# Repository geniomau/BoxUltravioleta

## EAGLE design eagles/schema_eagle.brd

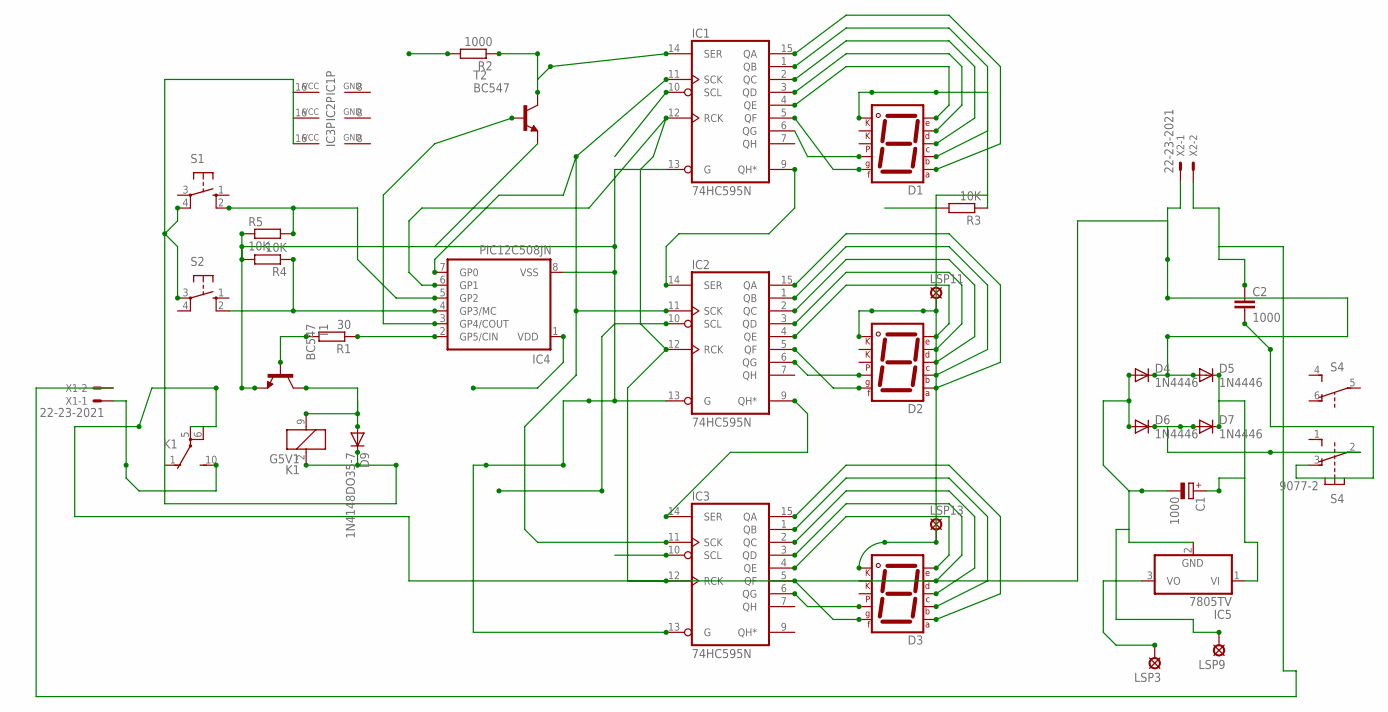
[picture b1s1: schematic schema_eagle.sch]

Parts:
C1: 1000; E5-10,5
C2: 1000; C22.5B7
D1, D2, D3: 7SEG-CK; 7SEG-13
D4, D5, D6, D7: 1N4446; DO35-10
D9: 1N4148DO35-7; DO35-7
IC1, IC2, IC3: 74HC595N; DIL16
IC4: PIC12C508JN; DIL8
IC5: 7805TV; TO220V
K1: G5V1
LSP3: VDD; LSP10
LSP9: GND; LSP10
LSP11, LSP13: 5V; LSP10
R1: 30; 0207/7
R2: 1000; 0207/7
R3, R4, R5: 10K; 0207/7
S1, S2: 10-XX; B3F-10XX
S4: 9077-2
T1, T2: BC547; TO92
X1, X2: 22-23-2021

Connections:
GND: C1.-, D4.A, D6.A, IC1.8 (GND), IC1.13 (G), IC2.8 (GND), IC2.13 (G), IC3.8 (GND), IC3.13 (G), IC4.8 (VSS), IC5.2 (GND), LSP9.MP, R3.2, R4.2, R5.1, T1.1 (E), T2.1 (E)
unnamed: D1.7 (A), IC1.15 (QA)
unnamed: D1.6 (B), IC1.1 (QB)
unnamed: D1.4 (C), IC1.2 (QC)
unnamed: D1.2 (D), IC1.3 (QD)
unnamed: D1.1 (E), IC1.4 (QE)
unnamed: D1.9 (F), IC1.5 (QF)
unnamed: D1.10 (G), IC1.6 (QG)
unnamed: D2.7 (A), IC2.15 (QA)
unnamed: D2.6 (B), IC2.1 (QB)
unnamed: D2.4 (C), IC2.2 (QC)
unnamed: D2.2 (D), IC2.3 (QD)
unnamed: D2.1 (E), IC2.4 (QE)
unnamed: D2.9 (F), IC2.5 (QF)
unnamed: D2.10 (G), IC2.6 (QG)
unnamed: D3.7 (A), IC3.15 (QA)
unnamed: D3.6 (B), IC3.1 (QB)
unnamed: D3.4 (C), IC3.2 (QC)
unnamed: D3.2 (D), IC3.3 (QD)
unnamed: D3.1 (E), IC3.4 (QE)
unnamed: D3.9 (F), IC3.5 (QF)
unnamed: D3.10 (G), IC3.6 (QG)
unnamed: C2.2, S4.3 (O)
unnamed: IC4.4 (GP3/MC), R4.1, S2.2 (S1)
unnamed: IC4.5 (GP2), R5.2, S1.2 (S1)
unnamed: IC1.12 (RCK), IC2.12 (RCK), IC3.12 (RCK), IC4.6 (GP1)
unnamed: IC1.11 (SCK), IC2.11 (SCK), IC3.11 (SCK), IC4.7 (GP0)
unnamed: IC1.14 (SER), R2.1, T2.3 (C)
unnamed: K1.10 (S), X1.1
unnamed: R1.2, T1.2 (B)
unnamed: IC1.9 (QH*), IC2.14 (SER)
unnamed: IC2.9 (QH*), IC3.14 (SER)
unnamed: IC4.3 (GP4/COUT), T2.2 (B)
unnamed: D9.A, K1.9 (2), T1.3 (C)
unnamed: IC4.2 (GP5/CIN), R1.1
unnamed: D4.C, D5.A, K1.5, K1.6, X2.1
unnamed: D1.8 (CK2), D2.8 (CK2), D3.8 (CK2), LSP11.MP, LSP13.MP, R3.1
unnamed: C1.+, D5.C, D7.C, IC5.1 (VI)
unnamed: C2.1, X1.2, X2.2
unnamed: D6.C, D7.A, S4.2
VDD: D9.C, IC1.10 (SCL), IC1.16 (VCC), IC2.10 (SCL), IC2.16 (VCC), IC3.10 (SCL), IC3.16 (VCC), IC4.1 (VDD), IC5.3 (VO), K1.2 (1), LSP3.MP, R2.2, S1.4 (P1), S2.3

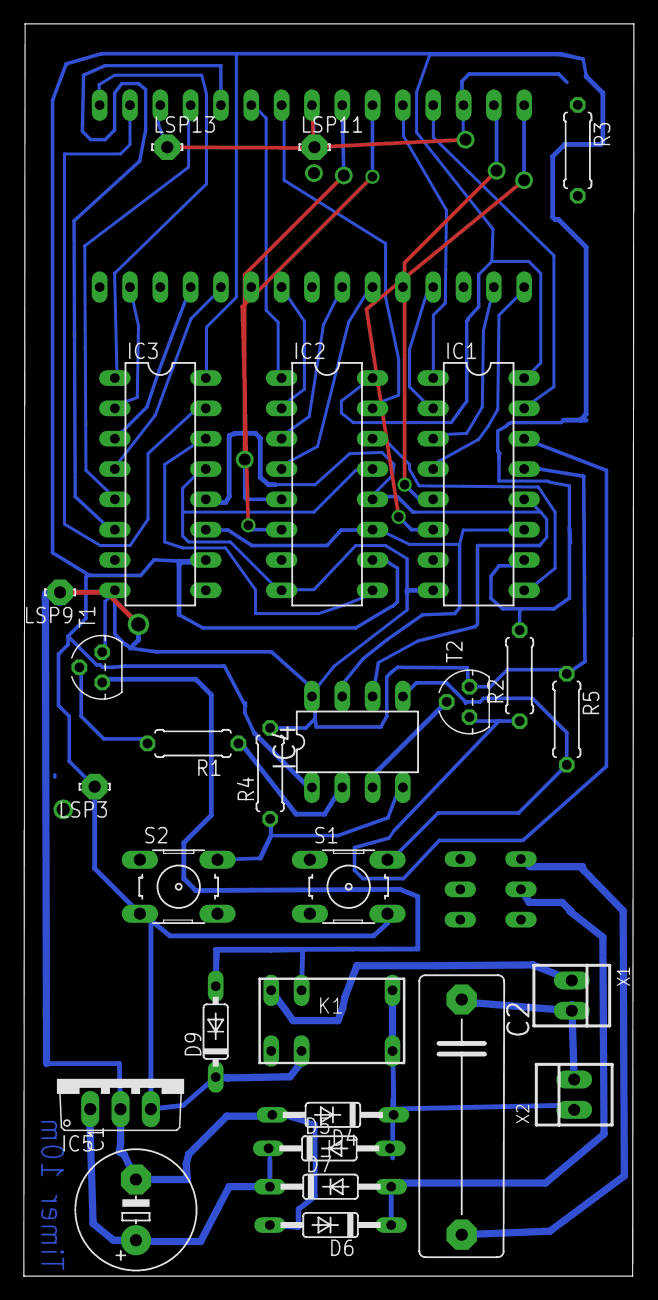
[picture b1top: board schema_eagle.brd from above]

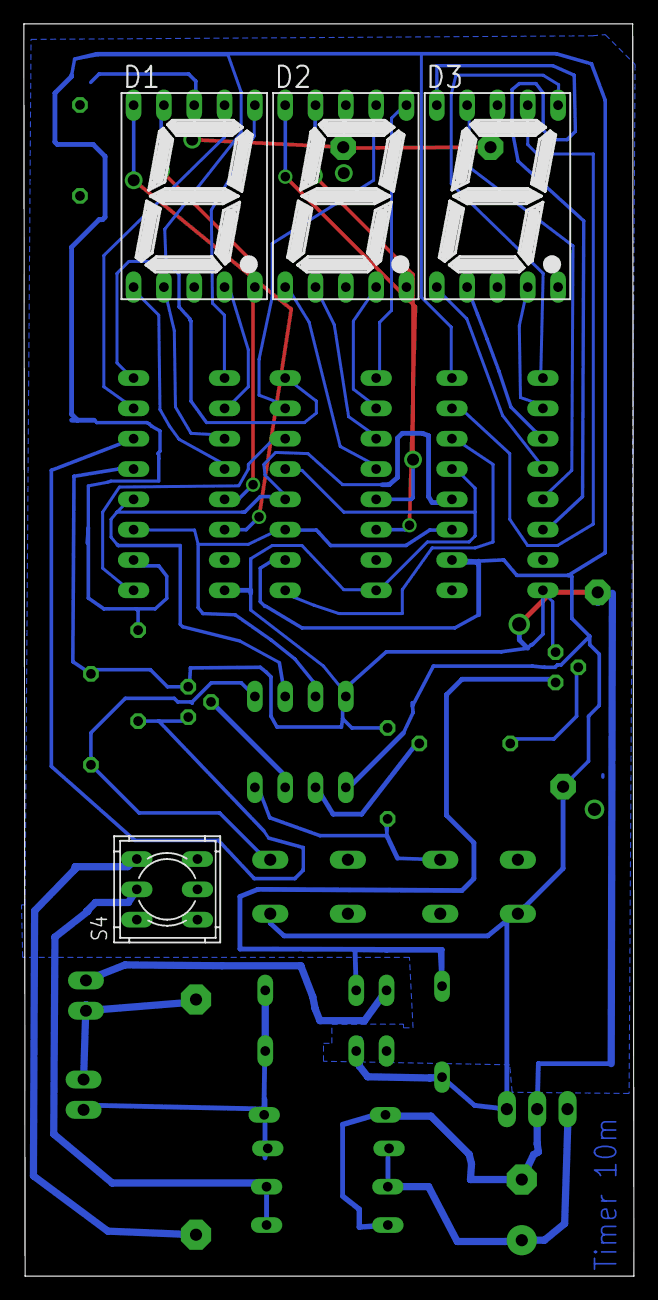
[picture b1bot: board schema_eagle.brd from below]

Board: 2 copper layers, 51.1 x 104.9 mm, 32 parts (4 on the bottom side), 41 nets.

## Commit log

2015-06-03 :lollipop: Added .gitattributes
2015-06-03 Arquivos de construcao
